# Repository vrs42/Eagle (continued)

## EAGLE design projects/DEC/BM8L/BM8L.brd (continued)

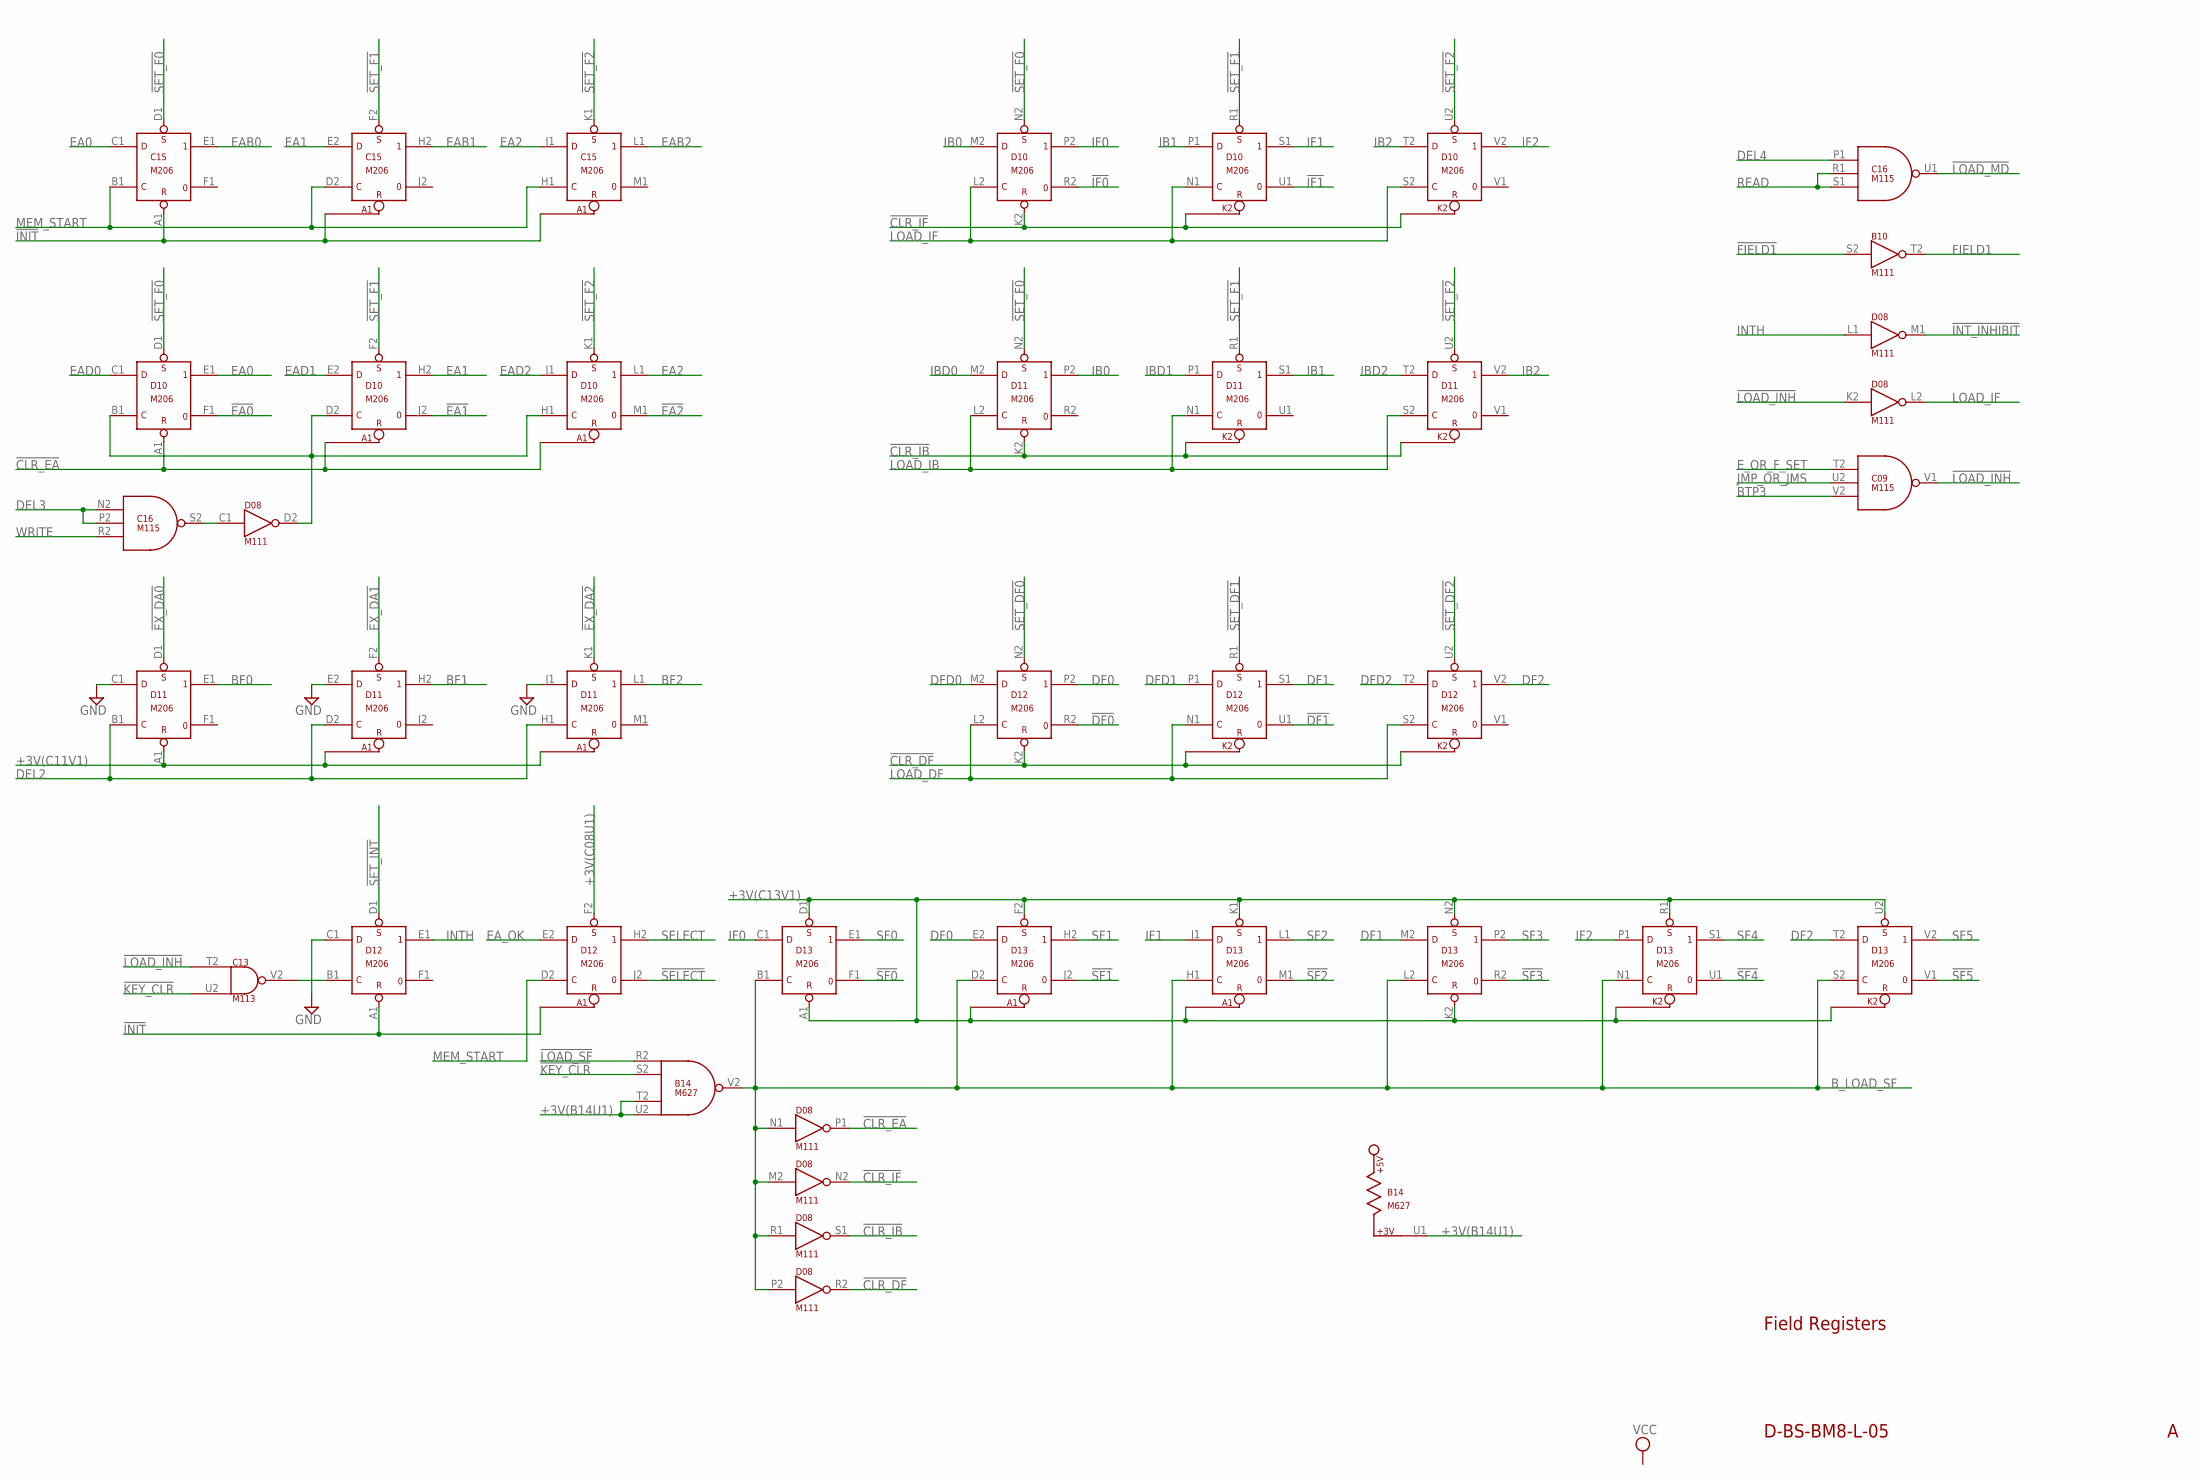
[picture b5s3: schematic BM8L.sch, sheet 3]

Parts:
B10: M111; H807
B14: M627; H807
C09, C16: M115; H807
C13: M113; H807
C15: M206; H807
D08: M111; H807
D10, D11, D12, D13: M206; H807

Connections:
!CLR_DF: D08.R2 (OUT), D12.K2 (R)
!CLR_EA: D08.P1 (OUT), D10.A1 (R)
!CLR_IB: D08.S1 (OUT), D11.K2 (R)
!CLR_IF: D08.N2 (OUT), D10.K2 (R)
!DF0: D12.R2 (0); also elsewhere on the board
!DF1: D12.U1 (0); also elsewhere on the board
!EA0: D10.F1 (0); also elsewhere on the board
!EA1: D10.J2 (0); also elsewhere on the board
!EA2: D10.M1 (0); also elsewhere on the board
!EX_DA0: D11.D1 (S); also elsewhere on the board
!EX_DA1: D11.F2 (S); also elsewhere on the board
!EX_DA2: D11.K1 (S); also elsewhere on the board
!FIELD1: B10.S2 (IN); also elsewhere on the board
!IF0: D10.R2 (0); also elsewhere on the board
!IF1: D10.U1 (0); also elsewhere on the board
!INIT: C15.A1 (R), D12.A1 (R); also elsewhere on the board
!INT_INHIBIT: D08.M1 (OUT); also elsewhere on the board
!KEY_CLR: B14.S2 (IN2), C13.U2 (IN2); also elsewhere on the board
!LOAD_INH: C09.V1 (OUT), C13.T2 (IN1), D08.K2 (IN)
!LOAD_MD: C16.U1 (OUT); also elsewhere on the board
!LOAD_SF: B14.R2 (IN1); also elsewhere on the board
!SELECT: D12.J2 (0); also elsewhere on the board
!SET_DF0: D12.N2 (S); also elsewhere on the board
!SET_DF1: D12.R1 (S); also elsewhere on the board
!SET_DF2: D12.U2 (S); also elsewhere on the board
!SET_F0: C15.D1 (S), D10.D1 (S), D10.N2 (S), D11.N2 (S); also elsewhere on the board
!SET_F1: C15.F2 (S), D10.F2 (S), D10.R1 (S), D11.R1 (S); also elsewhere on the board
!SET_F2: C15.K1 (S), D10.K1 (S), D10.U2 (S), D11.U2 (S); also elsewhere on the board
!SET_INT: D12.D1 (S); also elsewhere on the board
!SF0: D13.F1 (0); also elsewhere on the board
!SF1: D13.J2 (0); also elsewhere on the board
!SF2: D13.M1 (0); also elsewhere on the board
!SF3: D13.R2 (0); also elsewhere on the board
!SF4: D13.U1 (0); also elsewhere on the board
!SF5: D13.V1 (0); also elsewhere on the board
+3V(B14U1): B14.T2 (IN3), B14.U1, B14.U2 (IN4); also elsewhere on the board
+3V(C08U1): D12.F2 (S); also elsewhere on the board
+3V(C11V1): D11.A1 (R); also elsewhere on the board
+3V(C13V1): D13.A1 (R), D13.D1 (S), D13.F2 (S), D13.K1 (S), D13.K2 (R), D13.N2 (S), D13.R1 (S), D13.U2 (S); also elsewhere on the board
BF0: D11.E1 (1); also elsewhere on the board
BF1: D11.H2 (1); also elsewhere on the board
BF2: D11.L1 (1); also elsewhere on the board
BTP3: C09.V2 (IN3); also elsewhere on the board
B_LOAD_SF: B14.V2 (OUT), D08.M2 (IN), D08.N1 (IN), D08.P2 (IN), D08.R1 (IN), D13.B1 (C), D13.D2 (C), D13.H1 (C), D13.L2 (C), D13.N1 (C), D13.S2 (C)
DEL2: D11.B1 (C), D11.D2 (C), D11.H1 (C); also elsewhere on the board
DEL3: C16.N2 (IN1), C16.P2 (IN2); also elsewhere on the board
DEL3WRT: D08.D2 (OUT), D10.B1 (C), D10.D2 (C), D10.H1 (C)
DEL4: C16.P1 (IN1); also elsewhere on the board
DF0: D12.P2 (1), D13.E2 (D); also elsewhere on the board
DF1: D12.S1 (1), D13.M2 (D); also elsewhere on the board
DF2: D12.V2 (1), D13.T2 (D); also elsewhere on the board
DFD0: D12.M2 (D); also elsewhere on the board
DFD1: D12.P1 (D); also elsewhere on the board
DFD2: D12.T2 (D); also elsewhere on the board
EA0: C15.C1 (D), D10.E1 (1); also elsewhere on the board
EA1: C15.E2 (D), D10.H2 (1); also elsewhere on the board
EA2: C15.J1 (D), D10.L1 (1); also elsewhere on the board
EAB0: C15.E1 (1); also elsewhere on the board
EAB1: C15.H2 (1); also elsewhere on the board
EAB2: C15.L1 (1); also elsewhere on the board
EAD0: D10.C1 (D); also elsewhere on the board
EAD1: D10.E2 (D); also elsewhere on the board
EAD2: D10.J1 (D); also elsewhere on the board
EA_OK: D12.E2 (D); also elsewhere on the board
E_OR_F_SET: C09.T2 (IN1); also elsewhere on the board
FIELD1: B10.T2 (OUT); also elsewhere on the board
GND: B10.C2 (GND), B10.T1 (GND), B14.C2 (GND), B14.T1 (GND), C09.C2 (GND), C09.T1 (GND), C13.C2 (GND), C13.T1 (GND), C15.C2 (GND), C15.T1 (GND), C16.C2 (GND), C16.T1 (GND), D08.C2 (GND), D08.T1 (GND), D10.C2 (GND), D10.T1 (GND), D11.C1 (D), D11.C2 (GND), D11.E2 (D), D11.J1 (D), D11.T1 (GND), D12.C1 (D), D12.C2 (GND), D12.T1 (GND), D13.C2 (GND), D13.T1 (GND); also elsewhere on the board
IB0: D10.M2 (D), D11.P2 (1); also elsewhere on the board
IB1: D10.P1 (D), D11.S1 (1); also elsewhere on the board
IB2: D10.T2 (D), D11.V2 (1); also elsewhere on the board
IBD0: D11.M2 (D); also elsewhere on the board
IBD1: D11.P1 (D); also elsewhere on the board
IBD2: D11.T2 (D); also elsewhere on the board
IF0: D10.P2 (1), D13.C1 (D); also elsewhere on the board
IF1: D10.S1 (1), D13.J1 (D); also elsewhere on the board
IF2: D10.V2 (1), D13.P1 (D); also elsewhere on the board
INTH: D08.L1 (IN), D12.E1 (1)
JMP_OR_JMS: C09.U2 (IN2); also elsewhere on the board
LOAD_DF: D12.L2 (C), D12.N1 (C), D12.S2 (C); also elsewhere on the board
LOAD_IB: D11.L2 (C), D11.N1 (C), D11.S2 (C); also elsewhere on the board
LOAD_IF: D08.L2 (OUT), D10.L2 (C), D10.N1 (C), D10.S2 (C)
MEM_START: C15.B1 (C), C15.D2 (C), C15.H1 (C), D12.D2 (C); also elsewhere on the board
unnamed: C16.S2 (OUT), D08.C1 (IN)
unnamed: C13.V2 (OUT), D12.B1 (C)
READ: C16.R1 (IN2), C16.S1 (IN3); also elsewhere on the board
SELECT: D12.H2 (1); also elsewhere on the board
SF0: D13.E1 (1); also elsewhere on the board
SF1: D13.H2 (1); also elsewhere on the board
SF2: D13.L1 (1); also elsewhere on the board
SF3: D13.P2 (1); also elsewhere on the board
SF4: D13.S1 (1); also elsewhere on the board
SF5: D13.V2 (1); also elsewhere on the board
VCC: B10.A2 (VCC), B14.A2 (VCC), C09.A2 (VCC), C13.A2 (VCC), C15.A2 (VCC), C16.A2 (VCC), D08.A2 (VCC), D10.A2 (VCC), D11.A2 (VCC), D12.A2 (VCC), D13.A2 (VCC); also elsewhere on the board
WRITE: C16.R2 (IN3); also elsewhere on the board

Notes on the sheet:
D-BS-BM8-L-05
Field Registers

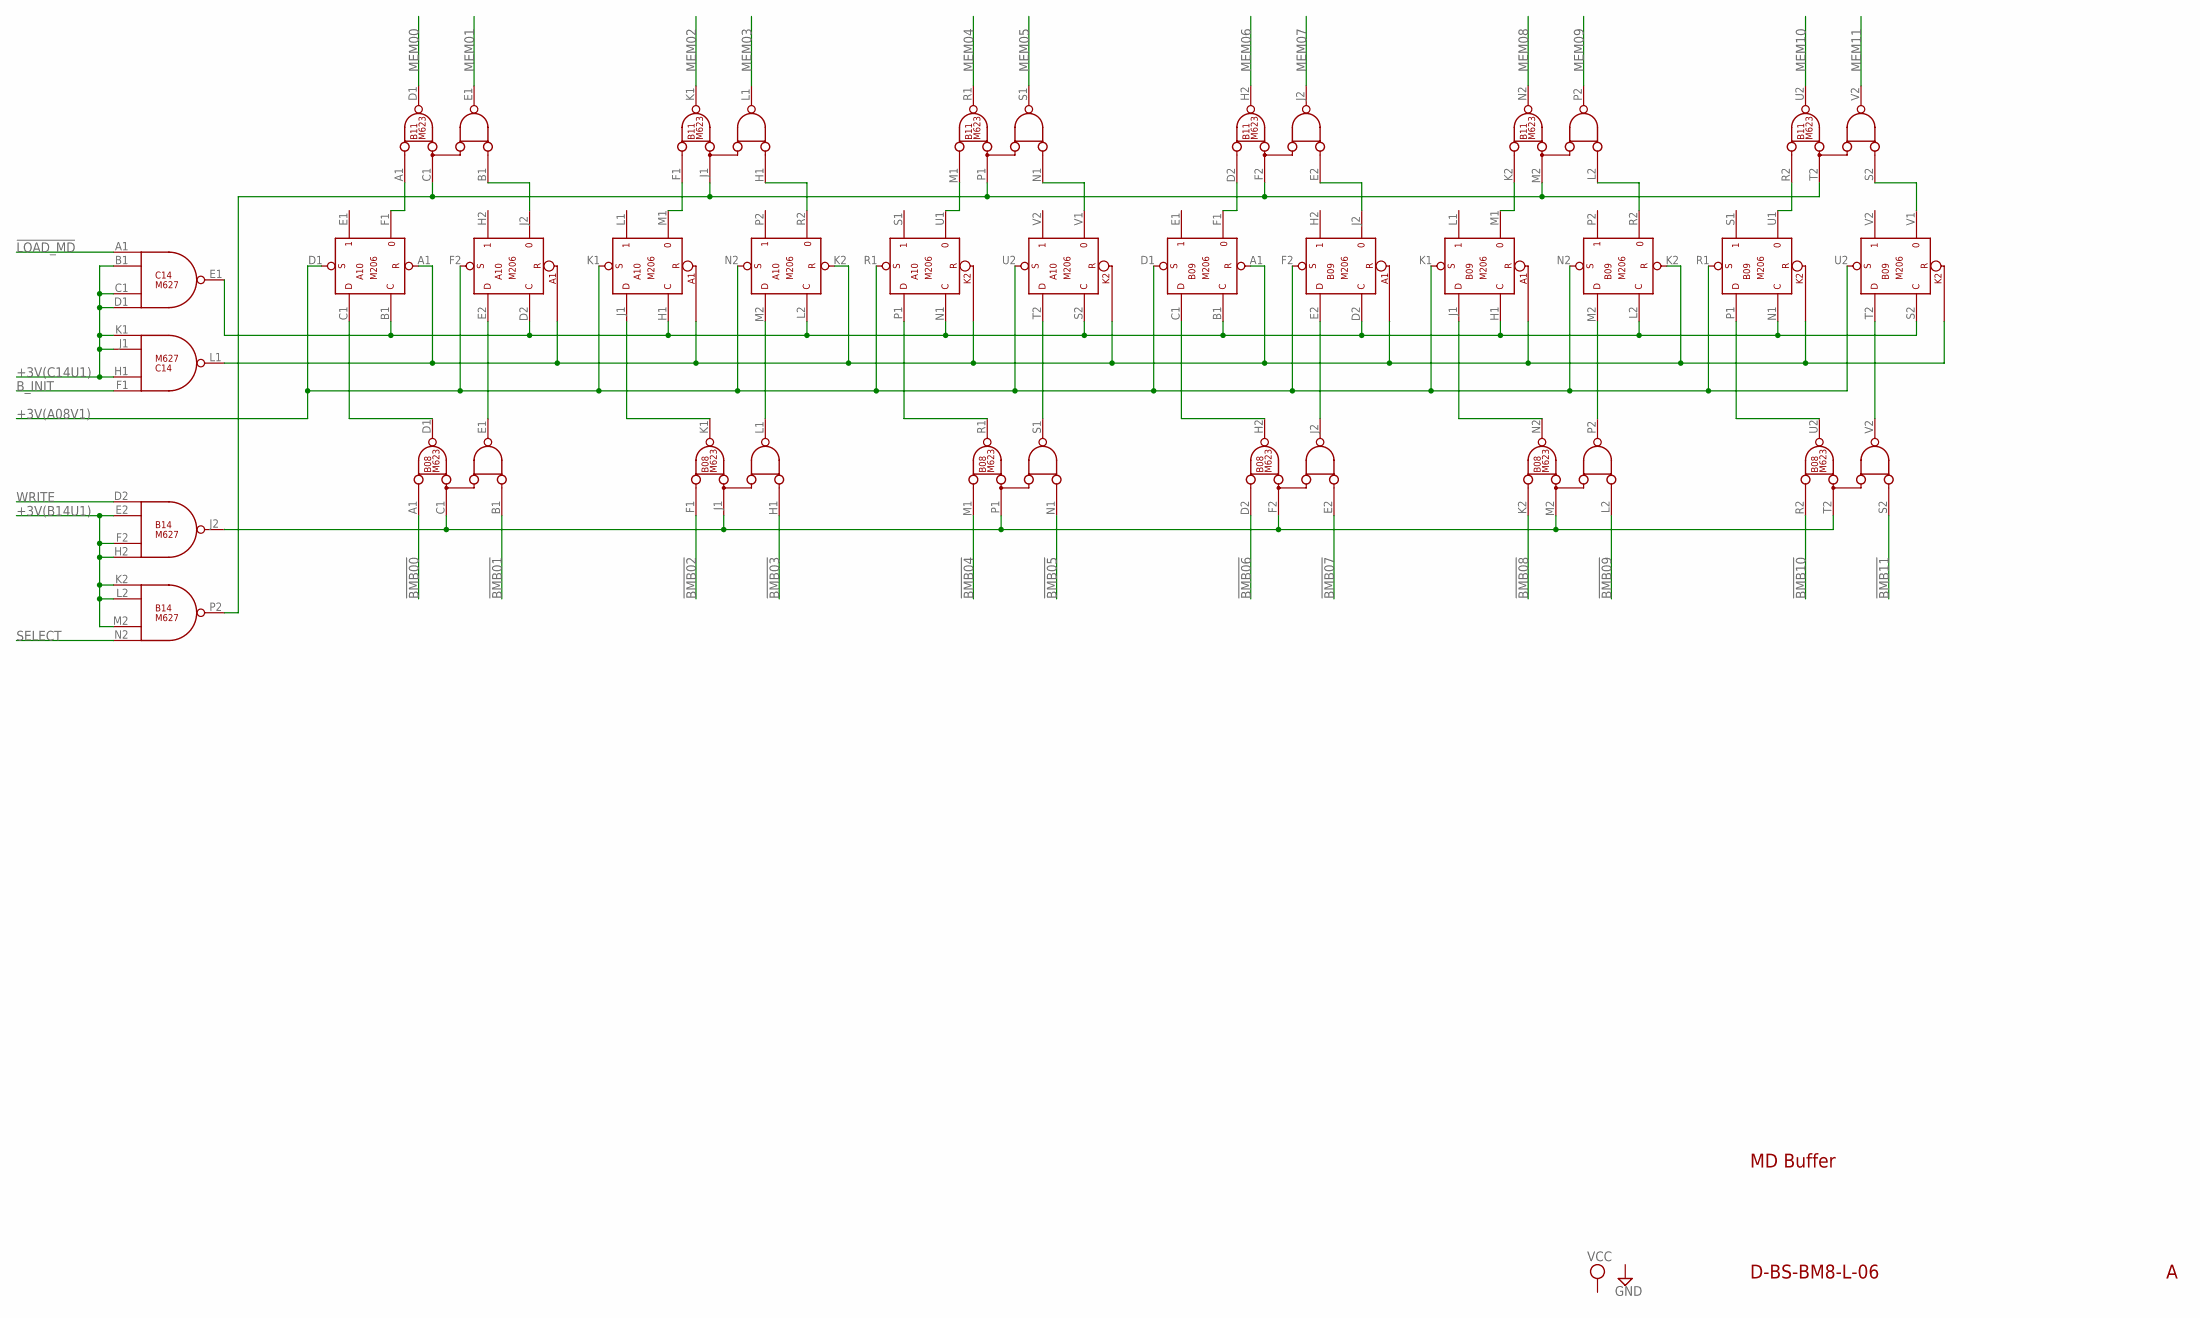
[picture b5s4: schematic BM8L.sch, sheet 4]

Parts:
A10: M206; H807
B08, B11: M623; H807
B09: M206; H807
B14: M627; H807
C14: M627; H807

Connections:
!BMB00: B08.A1 (A); also elsewhere on the board
!BMB01: B08.B1 (B); also elsewhere on the board
!BMB02: B08.F1 (A); also elsewhere on the board
!BMB03: B08.H1 (B); also elsewhere on the board
!BMB04: B08.M1 (A); also elsewhere on the board
!BMB05: B08.N1 (B); also elsewhere on the board
!BMB06: B08.D2 (A); also elsewhere on the board
!BMB07: B08.E2 (B); also elsewhere on the board
!BMB08: B08.K2 (A); also elsewhere on the board
!BMB09: B08.L2 (B); also elsewhere on the board
!BMB10: B08.R2 (A); also elsewhere on the board
!BMB11: B08.S2 (B); also elsewhere on the board
!LOAD_MD: C14.A1 (IN1); also elsewhere on the board
+3V(A08V1): A10.D1 (S), A10.F2 (S), A10.K1 (S), A10.N2 (S), A10.R1 (S), A10.U2 (S), B09.D1 (S), B09.F2 (S), B09.K1 (S), B09.N2 (S), B09.R1 (S), B09.U2 (S); also elsewhere on the board
+3V(B14U1): B14.E2 (IN2), B14.F2 (IN3), B14.H2 (IN4), B14.K2 (IN1), B14.L2 (IN2), B14.M2 (IN3); also elsewhere on the board
+3V(C14U1): C14.B1 (IN2), C14.C1 (IN3), C14.D1 (IN4), C14.H1 (IN2), C14.J1 (IN3), C14.K1 (IN4); also elsewhere on the board
B_INIT: C14.F1 (IN1); also elsewhere on the board
GND: A10.C2 (GND), A10.T1 (GND), B08.C2 (GND), B08.T1 (GND), B08.U1 (GND), B08.V1 (GND), B09.C2 (GND), B09.T1 (GND), B11.C2 (GND), B11.T1 (GND), B11.U1 (GND), B11.V1 (GND), B14.C2 (GND), B14.T1 (GND), C14.C2 (GND), C14.T1 (GND); also elsewhere on the board
MEM00: B11.D1 (D); also elsewhere on the board
MEM01: B11.E1 (E); also elsewhere on the board
MEM02: B11.K1 (D); also elsewhere on the board
MEM03: B11.L1 (E); also elsewhere on the board
MEM04: B11.R1 (D); also elsewhere on the board
MEM05: B11.S1 (E); also elsewhere on the board
MEM06: B11.H2 (D); also elsewhere on the board
MEM07: B11.J2 (E); also elsewhere on the board
MEM08: B11.N2 (D); also elsewhere on the board
MEM09: B11.P2 (E); also elsewhere on the board
MEM10: B11.U2 (D); also elsewhere on the board
MEM11: B11.V2 (E); also elsewhere on the board
unnamed: B11.C1 (C), B11.F2 (C), B11.J1 (C), B11.M2 (C), B11.P1 (C), B11.T2 (C), B14.P2 (OUT)
unnamed: A10.B1 (C), A10.D2 (C), A10.H1 (C), A10.L2 (C), A10.N1 (C), A10.S2 (C), B09.B1 (C), B09.D2 (C), B09.H1 (C), B09.L2 (C), B09.N1 (C), B09.S2 (C), C14.E1 (OUT)
unnamed: B08.C1 (C), B08.F2 (C), B08.J1 (C), B08.M2 (C), B08.P1 (C), B08.T2 (C), B14.J2 (OUT)
unnamed: A10.A1 (R), A10.K2 (R), B09.A1 (R), B09.K2 (R), C14.L1 (OUT)
unnamed: A10.C1 (D), B08.D1 (D)
unnamed: A10.E2 (D), B08.E1 (E)
unnamed: A10.J1 (D), B08.K1 (D)
unnamed: A10.M2 (D), B08.L1 (E)
unnamed: A10.T2 (D), B08.S1 (E)
unnamed: B08.J2 (E), B09.E2 (D)
unnamed: B08.H2 (D), B09.C1 (D)
unnamed: A10.P1 (D), B08.R1 (D)
unnamed: B08.N2 (D), B09.J1 (D)
unnamed: B08.P2 (E), B09.M2 (D)
unnamed: B08.U2 (D), B09.P1 (D)
unnamed: B08.V2 (E), B09.T2 (D)
unnamed: A10.U1 (0), B11.M1 (A)
unnamed: A10.V1 (0), B11.N1 (B)
unnamed: A10.F1 (0), B11.A1 (A)
unnamed: A10.J2 (0), B11.B1 (B)
unnamed: A10.M1 (0), B11.F1 (A)
unnamed: A10.R2 (0), B11.H1 (B)
unnamed: B09.F1 (0), B11.D2 (A)
unnamed: B09.J2 (0), B11.E2 (B)
unnamed: B09.M1 (0), B11.K2 (A)
unnamed: B09.R2 (0), B11.L2 (B)
unnamed: B09.U1 (0), B11.R2 (A)
unnamed: B09.V1 (0), B11.S2 (B)
SELECT: B14.N2 (IN4); also elsewhere on the board
VCC: A10.A2 (VCC), B08.A2 (VCC), B09.A2 (VCC), B11.A2 (VCC), B14.A2 (VCC), C14.A2 (VCC); also elsewhere on the board
WRITE: B14.D2 (IN1); also elsewhere on the board

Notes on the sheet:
D-BS-BM8-L-06
MD Buffer

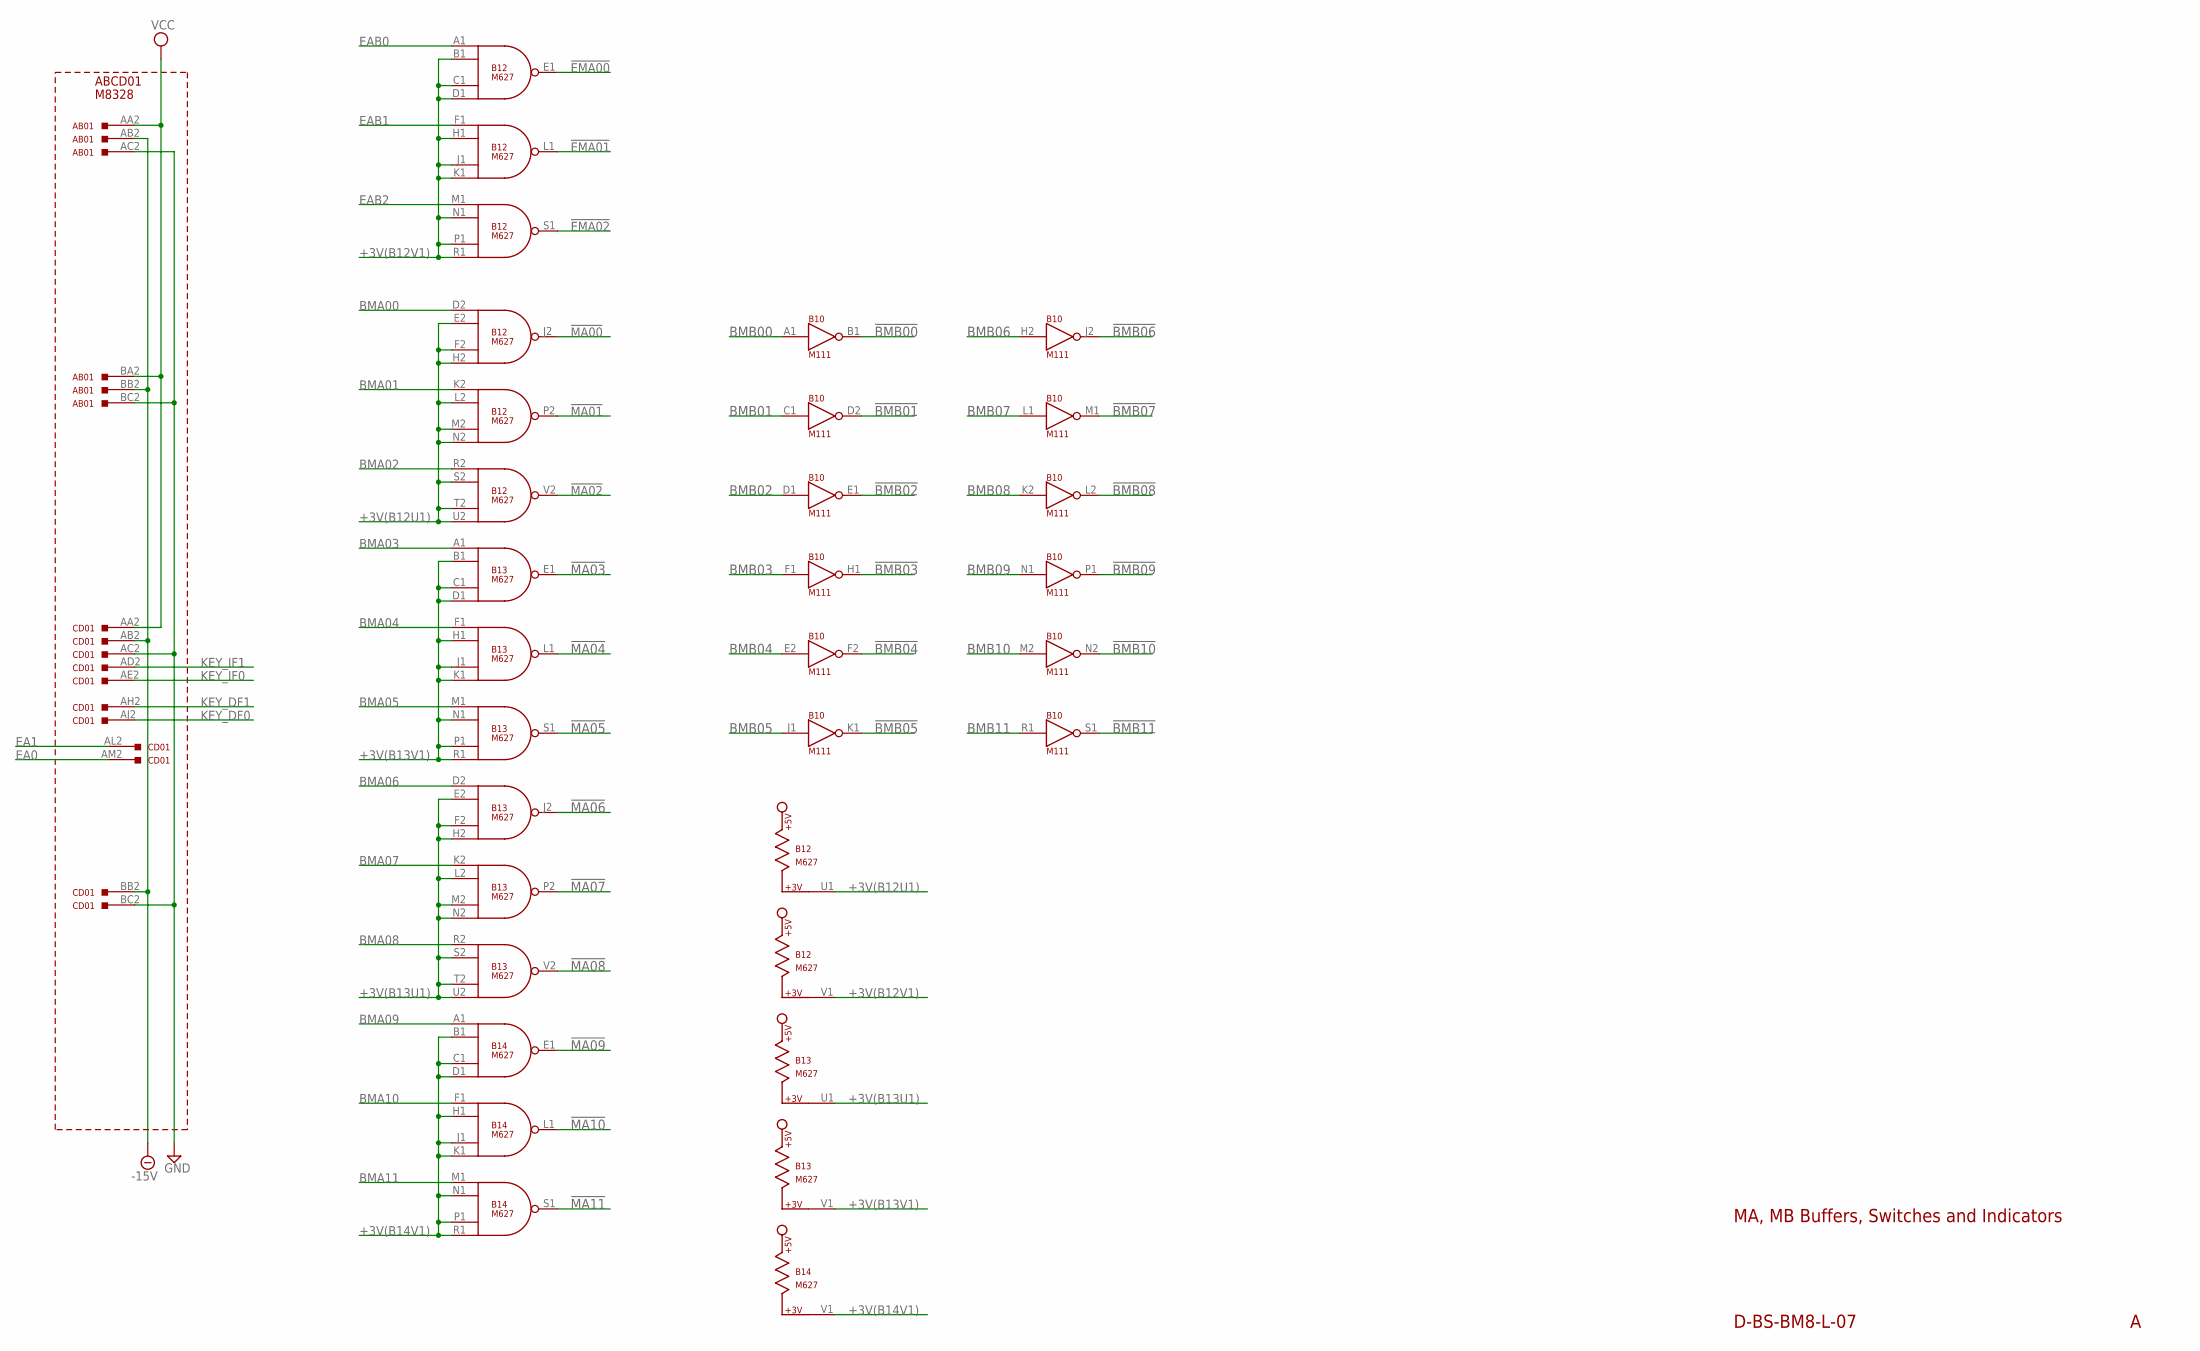
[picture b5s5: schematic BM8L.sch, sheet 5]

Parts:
AB01: M935; H807-2
B10: M111; H807
B12, B13, B14: M627; H807
CD01: M935; H807-2

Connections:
!BMB00: B10.B1 (OUT); also elsewhere on the board
!BMB01: B10.D2 (OUT); also elsewhere on the board
!BMB02: B10.E1 (OUT); also elsewhere on the board
!BMB03: B10.H1 (OUT); also elsewhere on the board
!BMB04: B10.F2 (OUT); also elsewhere on the board
!BMB05: B10.K1 (OUT); also elsewhere on the board
!BMB06: B10.J2 (OUT); also elsewhere on the board
!BMB07: B10.M1 (OUT); also elsewhere on the board
!BMB08: B10.L2 (OUT); also elsewhere on the board
!BMB09: B10.P1 (OUT); also elsewhere on the board
!BMB10: B10.N2 (OUT); also elsewhere on the board
!BMB11: B10.S1 (OUT); also elsewhere on the board
!EMA00: B12.E1 (OUT); also elsewhere on the board
!EMA01: B12.L1 (OUT); also elsewhere on the board
!EMA02: B12.S1 (OUT); also elsewhere on the board
!MA00: B12.J2 (OUT); also elsewhere on the board
!MA01: B12.P2 (OUT); also elsewhere on the board
!MA02: B12.V2 (OUT); also elsewhere on the board
!MA03: B13.E1 (OUT); also elsewhere on the board
!MA04: B13.L1 (OUT); also elsewhere on the board
!MA05: B13.S1 (OUT); also elsewhere on the board
!MA06: B13.J2 (OUT); also elsewhere on the board
!MA07: B13.P2 (OUT); also elsewhere on the board
!MA08: B13.V2 (OUT); also elsewhere on the board
!MA09: B14.E1 (OUT); also elsewhere on the board
!MA10: B14.L1 (OUT); also elsewhere on the board
!MA11: B14.S1 (OUT); also elsewhere on the board
+3V(B12U1): B12.E2 (IN2), B12.F2 (IN3), B12.H2 (IN4), B12.L2 (IN2), B12.M2 (IN3), B12.N2 (IN4), B12.S2 (IN2), B12.T2 (IN3), B12.U1, B12.U2 (IN4)
+3V(B12V1): B12.B1 (IN2), B12.C1 (IN3), B12.D1 (IN4), B12.H1 (IN2), B12.J1 (IN3), B12.K1 (IN4), B12.N1 (IN2), B12.P1 (IN3), B12.R1 (IN4), B12.V1
+3V(B13U1): B13.E2 (IN2), B13.F2 (IN3), B13.H2 (IN4), B13.L2 (IN2), B13.M2 (IN3), B13.N2 (IN4), B13.S2 (IN2), B13.T2 (IN3), B13.U1, B13.U2 (IN4)
+3V(B13V1): B13.B1 (IN2), B13.C1 (IN3), B13.D1 (IN4), B13.H1 (IN2), B13.J1 (IN3), B13.K1 (IN4), B13.N1 (IN2), B13.P1 (IN3), B13.R1 (IN4), B13.V1
+3V(B14V1): B14.B1 (IN2), B14.C1 (IN3), B14.D1 (IN4), B14.H1 (IN2), B14.J1 (IN3), B14.K1 (IN4), B14.N1 (IN2), B14.P1 (IN3), B14.R1 (IN4), B14.V1
-15V: AB01.AB2, AB01.BB2, CD01.AB2, CD01.BB2; also elsewhere on the board
BMA00: B12.D2 (IN1); also elsewhere on the board
BMA01: B12.K2 (IN1); also elsewhere on the board
BMA02: B12.R2 (IN1); also elsewhere on the board
BMA03: B13.A1 (IN1); also elsewhere on the board
BMA04: B13.F1 (IN1); also elsewhere on the board
BMA05: B13.M1 (IN1); also elsewhere on the board
BMA06: B13.D2 (IN1); also elsewhere on the board
BMA07: B13.K2 (IN1); also elsewhere on the board
BMA08: B13.R2 (IN1); also elsewhere on the board
BMA09: B14.A1 (IN1); also elsewhere on the board
BMA10: B14.F1 (IN1); also elsewhere on the board
BMA11: B14.M1 (IN1); also elsewhere on the board
BMB00: B10.A1 (IN); also elsewhere on the board
BMB01: B10.C1 (IN); also elsewhere on the board
BMB02: B10.D1 (IN); also elsewhere on the board
BMB03: B10.F1 (IN); also elsewhere on the board
BMB04: B10.E2 (IN); also elsewhere on the board
BMB05: B10.J1 (IN); also elsewhere on the board
BMB06: B10.H2 (IN); also elsewhere on the board
BMB07: B10.L1 (IN); also elsewhere on the board
BMB08: B10.K2 (IN); also elsewhere on the board
BMB09: B10.N1 (IN); also elsewhere on the board
BMB10: B10.M2 (IN); also elsewhere on the board
BMB11: B10.R1 (IN); also elsewhere on the board
EA0: CD01.AM2; also elsewhere on the board
EA1: CD01.AL2; also elsewhere on the board
EAB0: B12.A1 (IN1); also elsewhere on the board
EAB1: B12.F1 (IN1); also elsewhere on the board
EAB2: B12.M1 (IN1); also elsewhere on the board
GND: AB01.AC2, AB01.BC2, B10.C2 (GND), B10.T1 (GND), B12.C2 (GND), B12.T1 (GND), B13.C2 (GND), B13.T1 (GND), B14.C2 (GND), B14.T1 (GND), CD01.AC2, CD01.BC2; also elsewhere on the board
KEY_DF0: CD01.AJ2; also elsewhere on the board
KEY_DF1: CD01.AH2; also elsewhere on the board
KEY_IF0: CD01.AE2; also elsewhere on the board
KEY_IF1: CD01.AD2; also elsewhere on the board
VCC: AB01.AA2, AB01.BA2, B10.A2 (VCC), B12.A2 (VCC), B13.A2 (VCC), B14.A2 (VCC), CD01.AA2; also elsewhere on the board

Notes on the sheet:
D-BS-BM8-L-07
MA, MB Buffers, Switches and Indicators
M8328
ABCD01
